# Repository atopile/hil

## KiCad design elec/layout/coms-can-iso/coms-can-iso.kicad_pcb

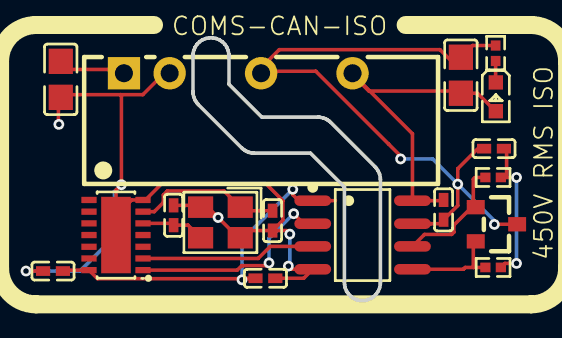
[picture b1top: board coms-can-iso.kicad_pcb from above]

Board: 2 copper layers, 17 parts (0 on the bottom side), 13 nets.

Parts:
C1: 2.2µF ±10% 50V X5R; C0805-3b2e55
C2: 10µF ±10% 25V X5R; C0805-3b2e55
D1: SOT-23_L2.9-W1.3-P1.90-LS2.4-BR-0c2373
D2: LED0603-RD-c81ffb
R1: 2kΩ ±1% 62.5mW; R0402-56259e
U1: VDFN-14_L4.5-W3.0-P0.65-BL-EP-99cb5b
U2, U12, U13: 1µF ±10% 25V X5R; C0402-b3ef17
U3: CRYSTAL-SMD_4P-L3.2-W2.5-BL-e199c8
U4, U5: 10pF ±5% 50V C0G; C0402-b3ef17
U6: PWRM-TH_BXXXXS-2WR3-d8b2fb
U9: 4.7nF ±10% 50V X7R; C0402-b3ef17
U10, U11: 1MΩ ±1% 62.5mW; R0402-56259e
U14: SOIC-8_L4.9-W3.9-P1.27-LS6.0-BL-6ccfeb

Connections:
CANH: D1.1, U10.1, U14.6
CANL: D1.2, U11.2, U14.5
_midpoint: U9.1, U10.2, U11.1
cathode: D2.1, R1.1
gnd: C1.2, U1.7, U1.15, U2.2, U3.2, U3.4, U4.2, U5.2, U6.2, U12.2, U14.4
gnd-1: C2.2, D1.3, R1.2, U6.4, U9.2, U13.2, U14.7
hv: C1.1, U6.1
hv-1: C2.1, D2.2, U6.6, U13.1, U14.8
hv-2: U1.14, U2.1, U12.1, U14.1
rx: U1.2, U14.3
tx: U1.1, U14.2
xin: U1.6, U3.1, U4.1
xout: U1.5, U3.3, U5.1

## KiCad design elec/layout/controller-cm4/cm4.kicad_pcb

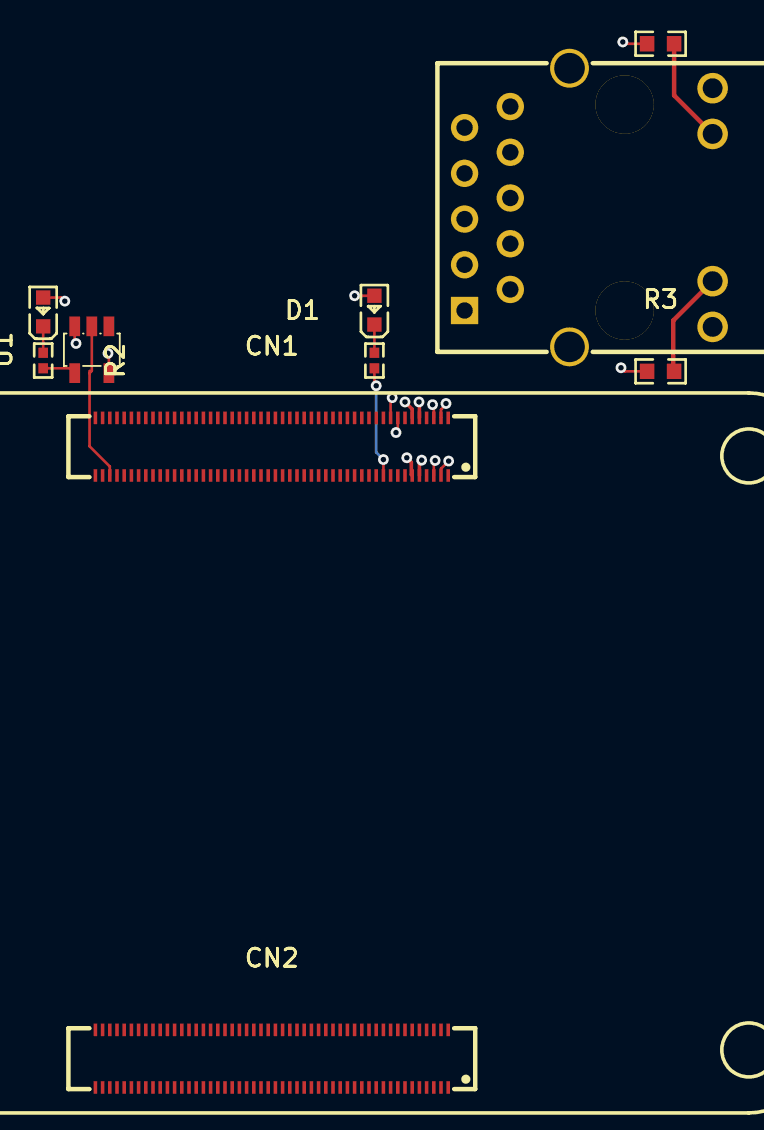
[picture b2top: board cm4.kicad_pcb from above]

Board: 4 copper layers, 10 parts (0 on the bottom side), 21 nets.

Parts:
CN1, CN2: CONN-SMD_DF40C-100DS-0.4V-51-ceffa9
D1: LED0603-RD-YELLOW-5af84a
D2: LED0603-RD-c81ffb
R1, R2: 10kΩ ±1% 62.5mW; R0402-56259e
R3, R4: 470Ω ±1% 100mW; R0603-ebcab9
RJ1: RJ45-TH_HR911130A-5845d4
U1: SOT-23-5_L3.0-W1.7-P0.95-LS2.8-BR-9d80aa

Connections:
ETH_LED_ACTIVITY: CN1.92, RJ1.14
ETH_LED_LINK: CN1.93, RJ1.11
ETH_P0_N: CN1.5, RJ1.P3
ETH_P0_P: CN1.6, RJ1.P2
ETH_P1_N: CN1.3, RJ1.P7
ETH_P1_P: CN1.2, RJ1.P4
ETH_P2_N: CN1.96, RJ1.P6
ETH_P2_P: CN1.95, RJ1.P5
ETH_P3_N: CN1.98, RJ1.P9
ETH_P3_P: CN1.99, RJ1.P8
PWR_LED: CN1.48, U1.2
VCC_1V8: CN1.44, CN1.45
VCC_3V3: CN1.39, CN1.42, CN1.43, D1.2, D2.2, R3.1, R4.1, U1.5
VCC_5V: CN1.57, CN1.58, CN1.59, CN1.60, CN1.61, CN1.62
cm4-cathode: D2.1, R2.1
cm4-cathode-1: D1.1, R1.1
cm4-line-5: R2.2, U1.4
gnd: CN1.1, CN1.4, CN1.7, CN1.11, CN1.16, CN1.21, CN1.26, CN1.30, CN1.33, CN1.37, CN1.49, CN1.65, CN1.68, CN1.71, CN1.74, CN1.79, CN1.84, CN1.89, CN1.90, CN1.94, CN1.97, CN1.100, CN2.4, CN2.7, CN2.10, CN2.13, CN2.16, CN2.19, CN2.22, CN2.28, CN2.31, CN2.34, CN2.37, CN2.40, CN2.43, CN2.46, CN2.49, CN2.52, CN2.55, CN2.58, CN2.61, CN2.64, CN2.67, CN2.70, CN2.73, CN2.82, CN2.85, CN2.88, CN2.91, CN2.94, CN2.97, RJ1.SHIELD0, RJ1.SHIELD1, U1.3
pins[19]: CN1.10, R1.2
rj45-anode: R3.2, RJ1.12
rj45-anode-1: R4.2, RJ1.13

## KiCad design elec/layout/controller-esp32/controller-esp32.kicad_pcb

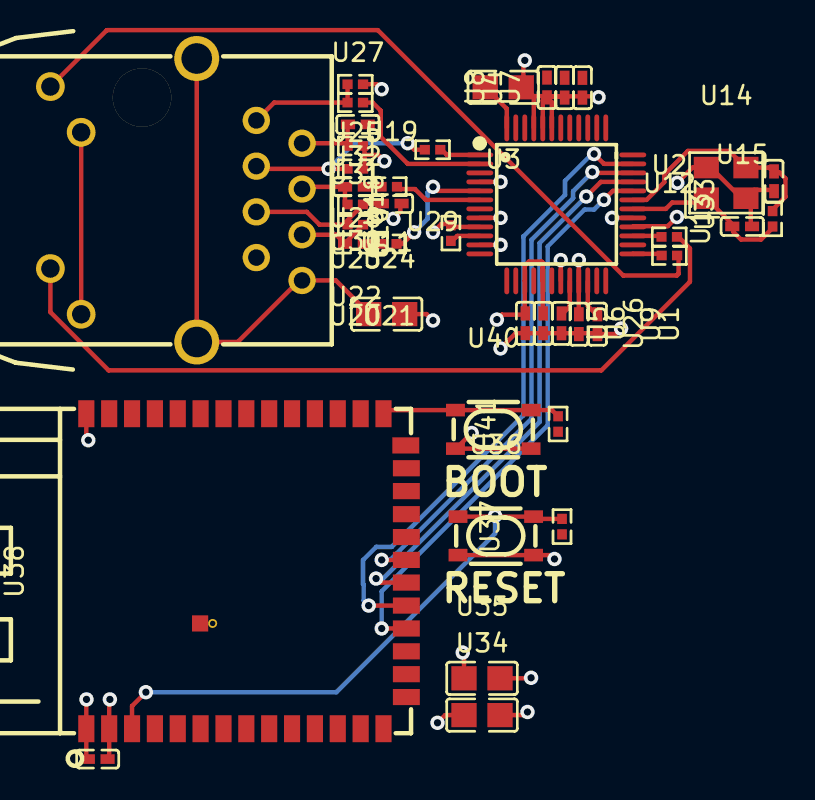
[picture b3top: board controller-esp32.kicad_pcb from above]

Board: 2 copper layers, 40 parts (0 on the bottom side), 30 nets.

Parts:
U1, U19: 10nF ±10% 50V X7R; C0402-b3ef17
U2, U12: 220Ω ±1% 62.5mW; R0402-56259e
U3, U34, U35: 10µF ±10% 25V X5R; C0805-3b2e55
U4, U5, U6, U7, U8, U9, U39: 100nF ±10% 16V X7R; C0402-b3ef17
U10: 12.4kΩ ±1% 62.5mW; R0402-56259e
U11: 1nF ±10% 50V X7R; C0805-3b2e55
U13: 1MΩ ±1% 62.5mW; R0402-56259e
U14: CRYSTAL-SMD_4P-L3.2-W2.5-BL
U15, U16: 10pF ±5% 50V C0G; C0402-b3ef17
U18: RJ45-TH_J1B1211CCD
U20, U23: 6.8nF ±10% 50V X7R; C0402-b3ef17
U21, U24, U29, U31: 33Ω ±1% 62.5mW; R0402-56259e
U22, U25, U30, U32: 49.9Ω ±1% 62.5mW; R0402-56259e
U26: 4.7µF ±10% 10V X5R; C0402-b3ef17
U27: 22nF ±10% 50V X7R; C0402-b3ef17
U28: 10Ω ±1% 62.5mW; R0402-56259e
U33: LQFP-48_L7.0-W7.0-P0.50-LS9.0-BL
U36, U40: KEY-SMD_4P-L4.2-W3.2-P2.20-LS4.6
U37, U41: 10kΩ ±1% 62.5mW; R0402-56259e
U38: WIRELM-SMD_ESP32-S3-WROOM-1

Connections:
ACTLED: U2.1, U33.27
CGND: U11.1, U18.8, U18.13, U18.14
EXRES1: U10.1, U33.10
LINKLED: U12.1, U33.25
LLED_minus: U12.2, U18.9
RCT: U18.5, U19.1, U22.2, U25.2
RD_minus: U18.6, U20.2, U22.1
RD_plus: U18.4, U23.2, U25.1
RLED_minus: U2.2, U18.11
RXN: U21.1, U33.5
RXP: U24.1, U33.6
TCT: U18.2, U27.1, U28.2
TD_minus: U18.3, U29.2, U30.2
TD_plus: U18.1, U31.2, U32.2
TOCAP: U26.1, U33.20
TXN: U29.1, U33.1
TXP: U31.1, U33.2
_1V2O: U1.1, U33.22
cs: U33.32, U38.18
ethernet-net: U20.1, U21.2
ethernet-net-1: U23.1, U24.2
gnd: U1.2, U3.2, U4.2, U5.2, U6.2, U7.2, U8.2, U9.2, U10.2, U11.2, U14.2, U14.4, U15.2, U16.2, U19.2, U26.2, U27.2, U33.3, U33.9, U33.14, U33.16, U33.19, U33.29, U33.48, U34.2, U35.2, U36.3, U36.4, U38.1, U38.40, U38.41, U39.2, U40.3, U40.4
hv: U3.1, U4.1, U5.1, U6.1, U7.1, U8.1, U9.1, U18.10, U18.12, U28.1, U30.1, U32.1, U33.4, U33.8, U33.11, U33.15, U33.17, U33.21, U33.28, U33.43, U33.44, U33.45, U34.1, U35.1, U37.1, U38.2, U39.1, U41.1
in: U36.1, U36.2, U37.2, U38.3
in-1: U38.27, U40.1, U40.2, U41.2
miso: U33.34, U38.21
mosi: U33.35, U38.19
sck: U33.33, U38.20
xin: U13.1, U14.1, U15.1, U33.30
xout: U13.2, U14.3, U16.1, U33.31

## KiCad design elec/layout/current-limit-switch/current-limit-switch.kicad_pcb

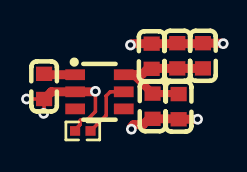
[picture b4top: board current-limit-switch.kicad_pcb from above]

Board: 2 copper layers, 8 parts (0 on the bottom side), 4 nets.

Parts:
C1, C2, C3, C4, C5, C6: 10µF ±10% 10V X5R; C0603-bd72f6
R1: 15kΩ ±1% 62.5mW; R0402-56259e
U1: SOT-23-6_L2.9-W1.6-P0.95-LS2.8-BR-bfc73b

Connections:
ILIM: R1.1, U1.5
IN: C1.1, U1.1
gnd: C1.2, C2.2, C3.2, C4.2, C5.2, C6.2, R1.2, U1.2
hv: C2.1, C3.1, C4.1, C5.1, C6.1, U1.6

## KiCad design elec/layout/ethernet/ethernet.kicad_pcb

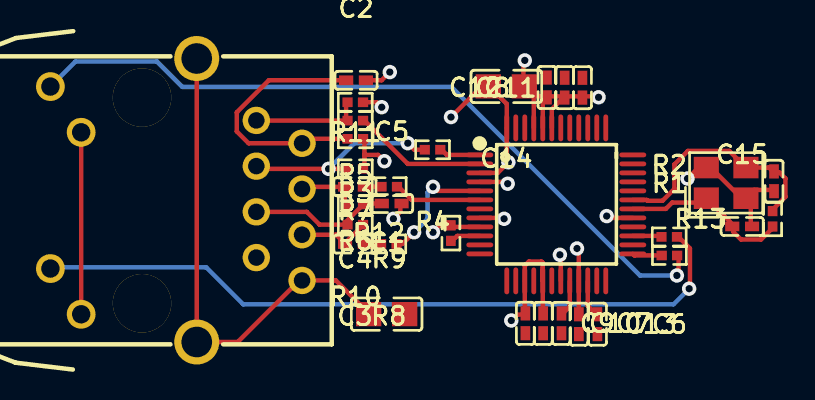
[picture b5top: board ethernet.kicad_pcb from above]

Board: 2 copper layers, 32 parts (0 on the bottom side), 24 nets.

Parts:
C1: 1nF ±10% 50V X7R; C0805-3b2e55
C2: 22nF ±10% 50V X7R; C0402-b3ef17
C3, C4: 6.8nF ±10% 50V X7R; C0402-b3ef17
C5, C6: 10nF ±10% 50V X7R; C0402-b3ef17
C7: 4.7µF ±10% 10V X5R; C0402-b3ef17
C8, C9, C10, C11, C12, C13: 100nF ±10% 16V X7R; C0402-b3ef17
C14: 10µF ±10% 25V X5R; C0805-3b2e55
C15, C16: 10pF ±5% 50V C0G; C0402-b3ef17
R1, R2: 220Ω ±1% 62.5mW; R0402-56259e
R3, R4, R8, R9: 33Ω ±1% 62.5mW; R0402-56259e
R5, R6, R10, R11: 49.9Ω ±1% 62.5mW; R0402-56259e
R7: 10Ω ±1% 62.5mW; R0402-56259e
R12: 12.4kΩ ±1% 62.5mW; R0402-56259e
R13: 1MΩ ±1% 62.5mW; R0402-56259e
U1: LQFP-48_L7.0-W7.0-P0.50-LS9.0-BL
U2: RJ45-TH_J1B1211CCD
U3: CRYSTAL-SMD_4P-L3.2-W2.5-BL

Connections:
ACTLED: R2.1, U1.27
CGND: C1.1, U2.8, U2.13, U2.14
EXRES1: R12.1, U1.10
LINKLED: R1.1, U1.25
LLED_minus: R1.2, U2.9
RCT: C5.1, R10.2, R11.2, U2.5
RD_minus: C3.2, R10.1, U2.6
RD_plus: C4.2, R11.1, U2.4
RLED_minus: R2.2, U2.11
RLED_plus: C8.1, C9.1, C10.1, C11.1, C12.1, C13.1, C14.1, R5.1, R6.1, R7.1, U1.4, U1.8, U1.11, U1.15, U1.17, U1.21, U1.28, U1.43, U1.44, U1.45, U2.10, U2.12
RXN: R8.1, U1.5
RXP: R9.1, U1.6
TCT: C2.1, R7.2, U2.2
TD_minus: R4.2, R6.2, U2.3
TD_plus: R3.2, R5.2, U2.1
TOCAP: C7.1, U1.20
TXN: R4.1, U1.1
TXP: R3.1, U1.2
_1V2O: C6.1, U1.22
gnd: C1.2, C2.2, C5.2, C6.2, C7.2, C8.2, C9.2, C10.2, C11.2, C12.2, C13.2, C14.2, C15.2, C16.2, R12.2, U1.3, U1.9, U1.14, U1.16, U1.19, U1.29, U1.48, U3.2, U3.4
net: C4.1, R9.2
net-1: C3.1, R8.2
xin: C15.1, R13.1, U1.30, U3.1
xout: C16.1, R13.2, U1.31, U3.3
